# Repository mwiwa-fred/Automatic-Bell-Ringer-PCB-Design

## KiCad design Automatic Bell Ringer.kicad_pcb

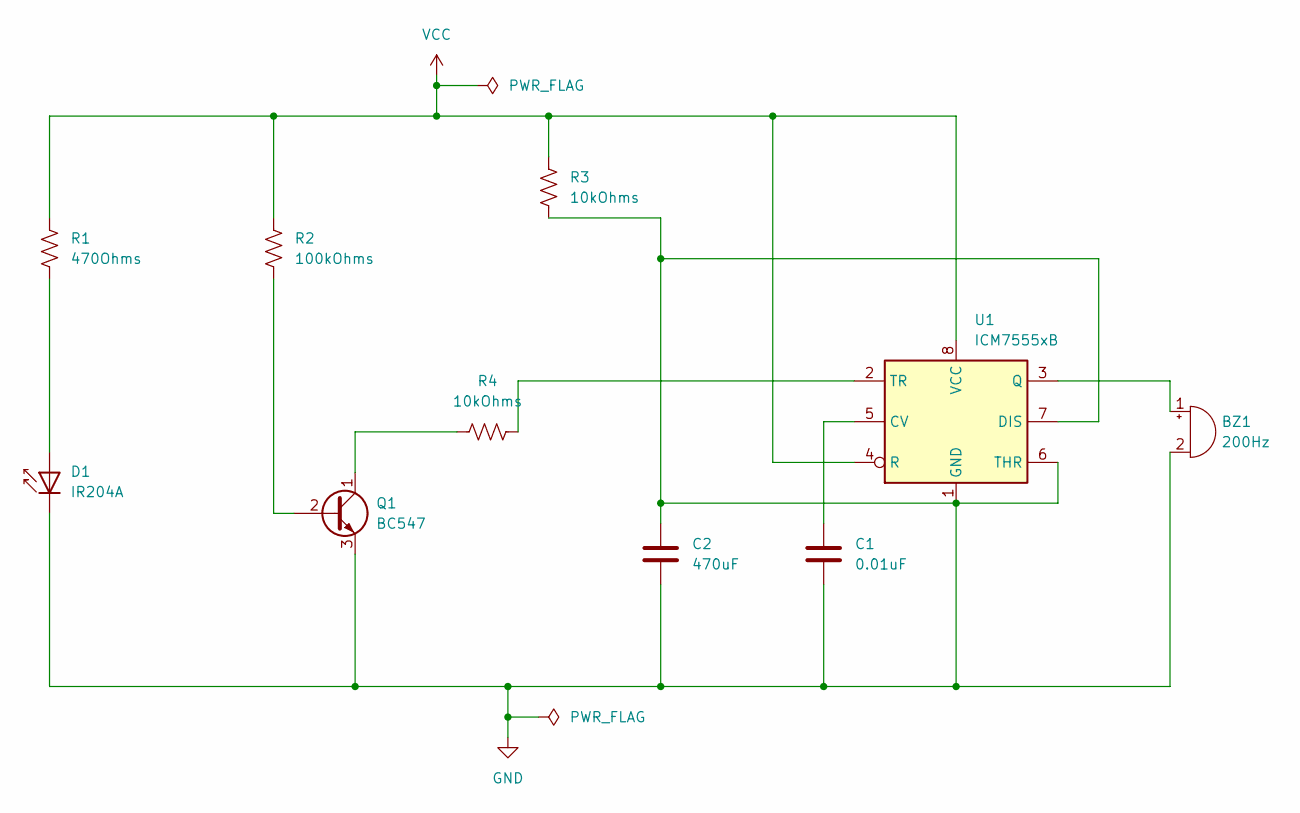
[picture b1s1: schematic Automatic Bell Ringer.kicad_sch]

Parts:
BZ1: 200Hz; SW_DIP_SPSTx01_Piano_10.8x4.1mm_W7.62mm_P2.54mm
C1: 0.01uF; CP_Axial_L10.0mm_D4.5mm_P15.00mm_Horizontal
C2: 470uF; CP_Axial_L10.0mm_D6.0mm_P15.00mm_Horizontal
D1: IR204A; LED_D3.0mm_IRBlack
Q1: BC547; TO-92_Inline
R1: 470Ohms; R_Axial_DIN0204_L3.6mm_D1.6mm_P1.90mm_Vertical
R2: 100kOhms; R_Axial_DIN0204_L3.6mm_D1.6mm_P2.54mm_Vertical
R3, R4: 10kOhms; R_Axial_DIN0204_L3.6mm_D1.6mm_P5.08mm_Vertical
U1: ICM7555xB; SOIC-8_3.9x4.9mm_P1.27mm

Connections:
GND: BZ1.2 (-), C1.2, C2.1, C2.2, D1.1 (K), Q1.3 (E), R3.2, U1.1 (GND), U1.6 (THR), U1.7 (DIS)
unnamed: BZ1.1 (+), U1.3 (Q)
unnamed: D1.2 (A), R1.2
unnamed: Q1.2 (B), R2.2
unnamed: Q1.1 (C), R4.2
unnamed: C1.1, U1.5 (CV)
unnamed: R4.1, U1.2 (TR)
VCC: R1.1, R2.1, R3.1, U1.4 (R), U1.8 (VCC)

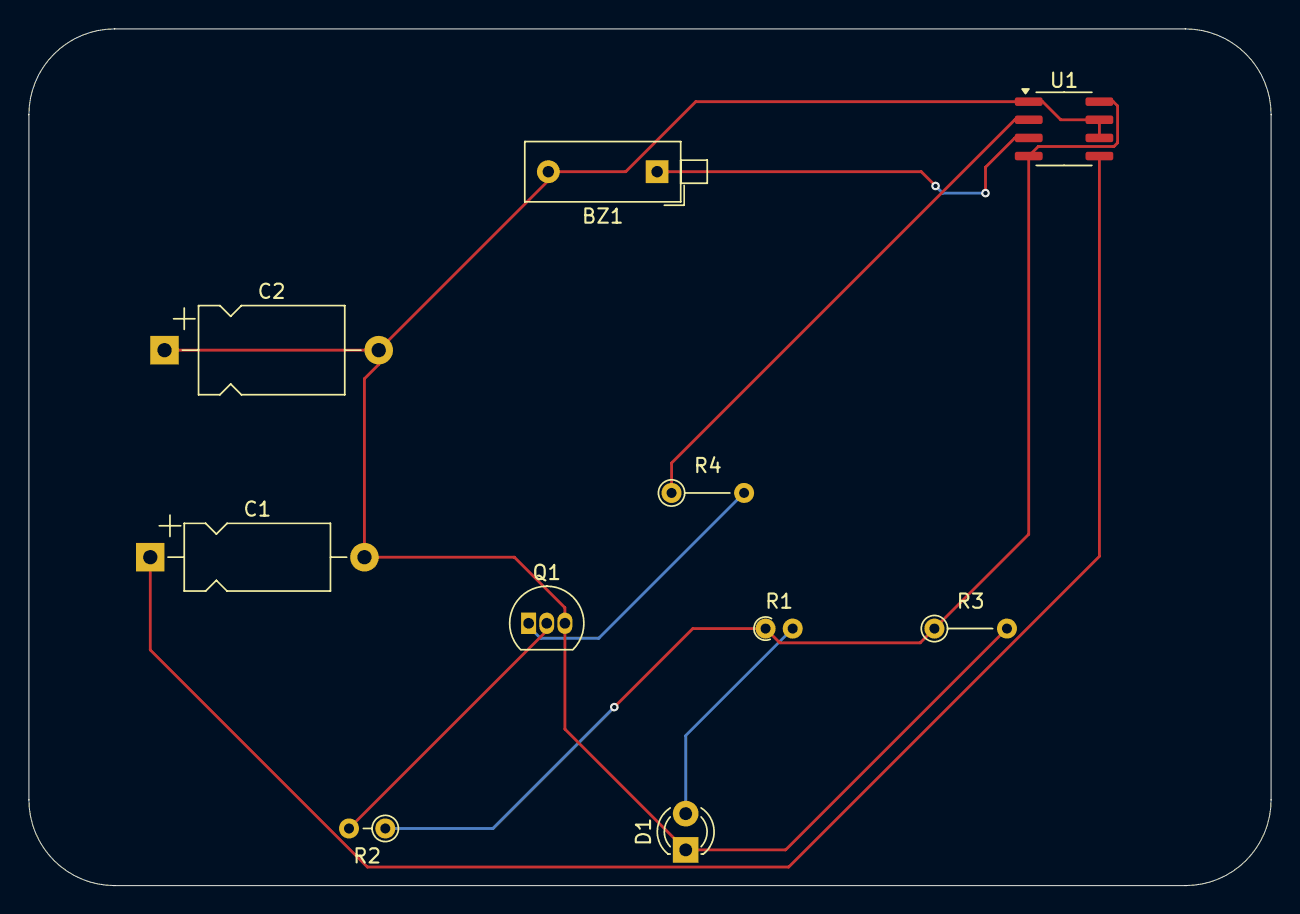
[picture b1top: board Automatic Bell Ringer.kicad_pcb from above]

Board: 2 copper layers, 87.0 x 60.0 mm, 10 parts (0 on the bottom side), 8 nets.
